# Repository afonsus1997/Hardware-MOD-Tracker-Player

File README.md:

# Hardware MOD Tracker Player

## How to setup the ST ARM toolchain and IDE

* [Download the GNU toolchain from arm](https://developer.arm.com/tools-and-software/open-source-software/developer-tools/gnu-toolchain/gnu-rm/downloads)

* Uninstall old packages 

```sudo apt remove binutils-arm-none-eabi gcc-arm-none-eabi libnewlib-arm-none-eabi```

* Untar package to desired directory (ex: ~/arm/)

```tar -xjvf gcc-arm-none-eabi-xxxxxxxxx```

* Add toolchain to path

```export PATH=$PATH:"PATH TO TOOLCHAIN"/bin/```

* Test arm-gcc

```arm-none-eabi-gcc --version```

### VSCODE Setup

* Install ```stm32-for-vscode``` plugin

* Install ```Cortex-Debug extension``` plugin

### Install STLINK drivers

* Install Libusb

```sudo apt-get install libusb-1.0-0-dev```

* Install stlink ultility

```git clone https://github.com/texane/stlink stlink.git
cd stlink
make
#install binaries:
sudo cp build/Release/st-* /usr/local/bin
#install udev rules
sudo cp etc/udev/rules.d/49-stlinkv* /etc/udev/rules.d/
#and restart udev
sudo udevadm control --reload
```

### Install openOCD

```sudo apt-get install openocd```

### Install STM32CUBEMX (Optional but recommended)

For pinmaps, code generation, etc...

* [Download STM32CUBEMX](https://my.st.com/content/my_st_com/en/products/development-tools/software-development-tools/stm32-software-development-tools/stm32-configurators-and-code-generators/)

* unzip and cd to extracted

* Mark binary as executable

```chmod +x SetupSTM32CubeMX-x.x.x.linux```

* Run binary

```./SetupSTM32CubeMX-x.x.x.linux```

* Go through installation process on GUI

## How to flash STM project

### Using VScode

* Open project folder

* Open command list (Ctrl+Shift+p)

* Type ```stm32``` and choose an option

### Using make

* Build

```make -f STM32Make.make```

* Build and flash

```make -f STM32Make.make flash```

* Clean 

```make -f STM32Make.make clean```

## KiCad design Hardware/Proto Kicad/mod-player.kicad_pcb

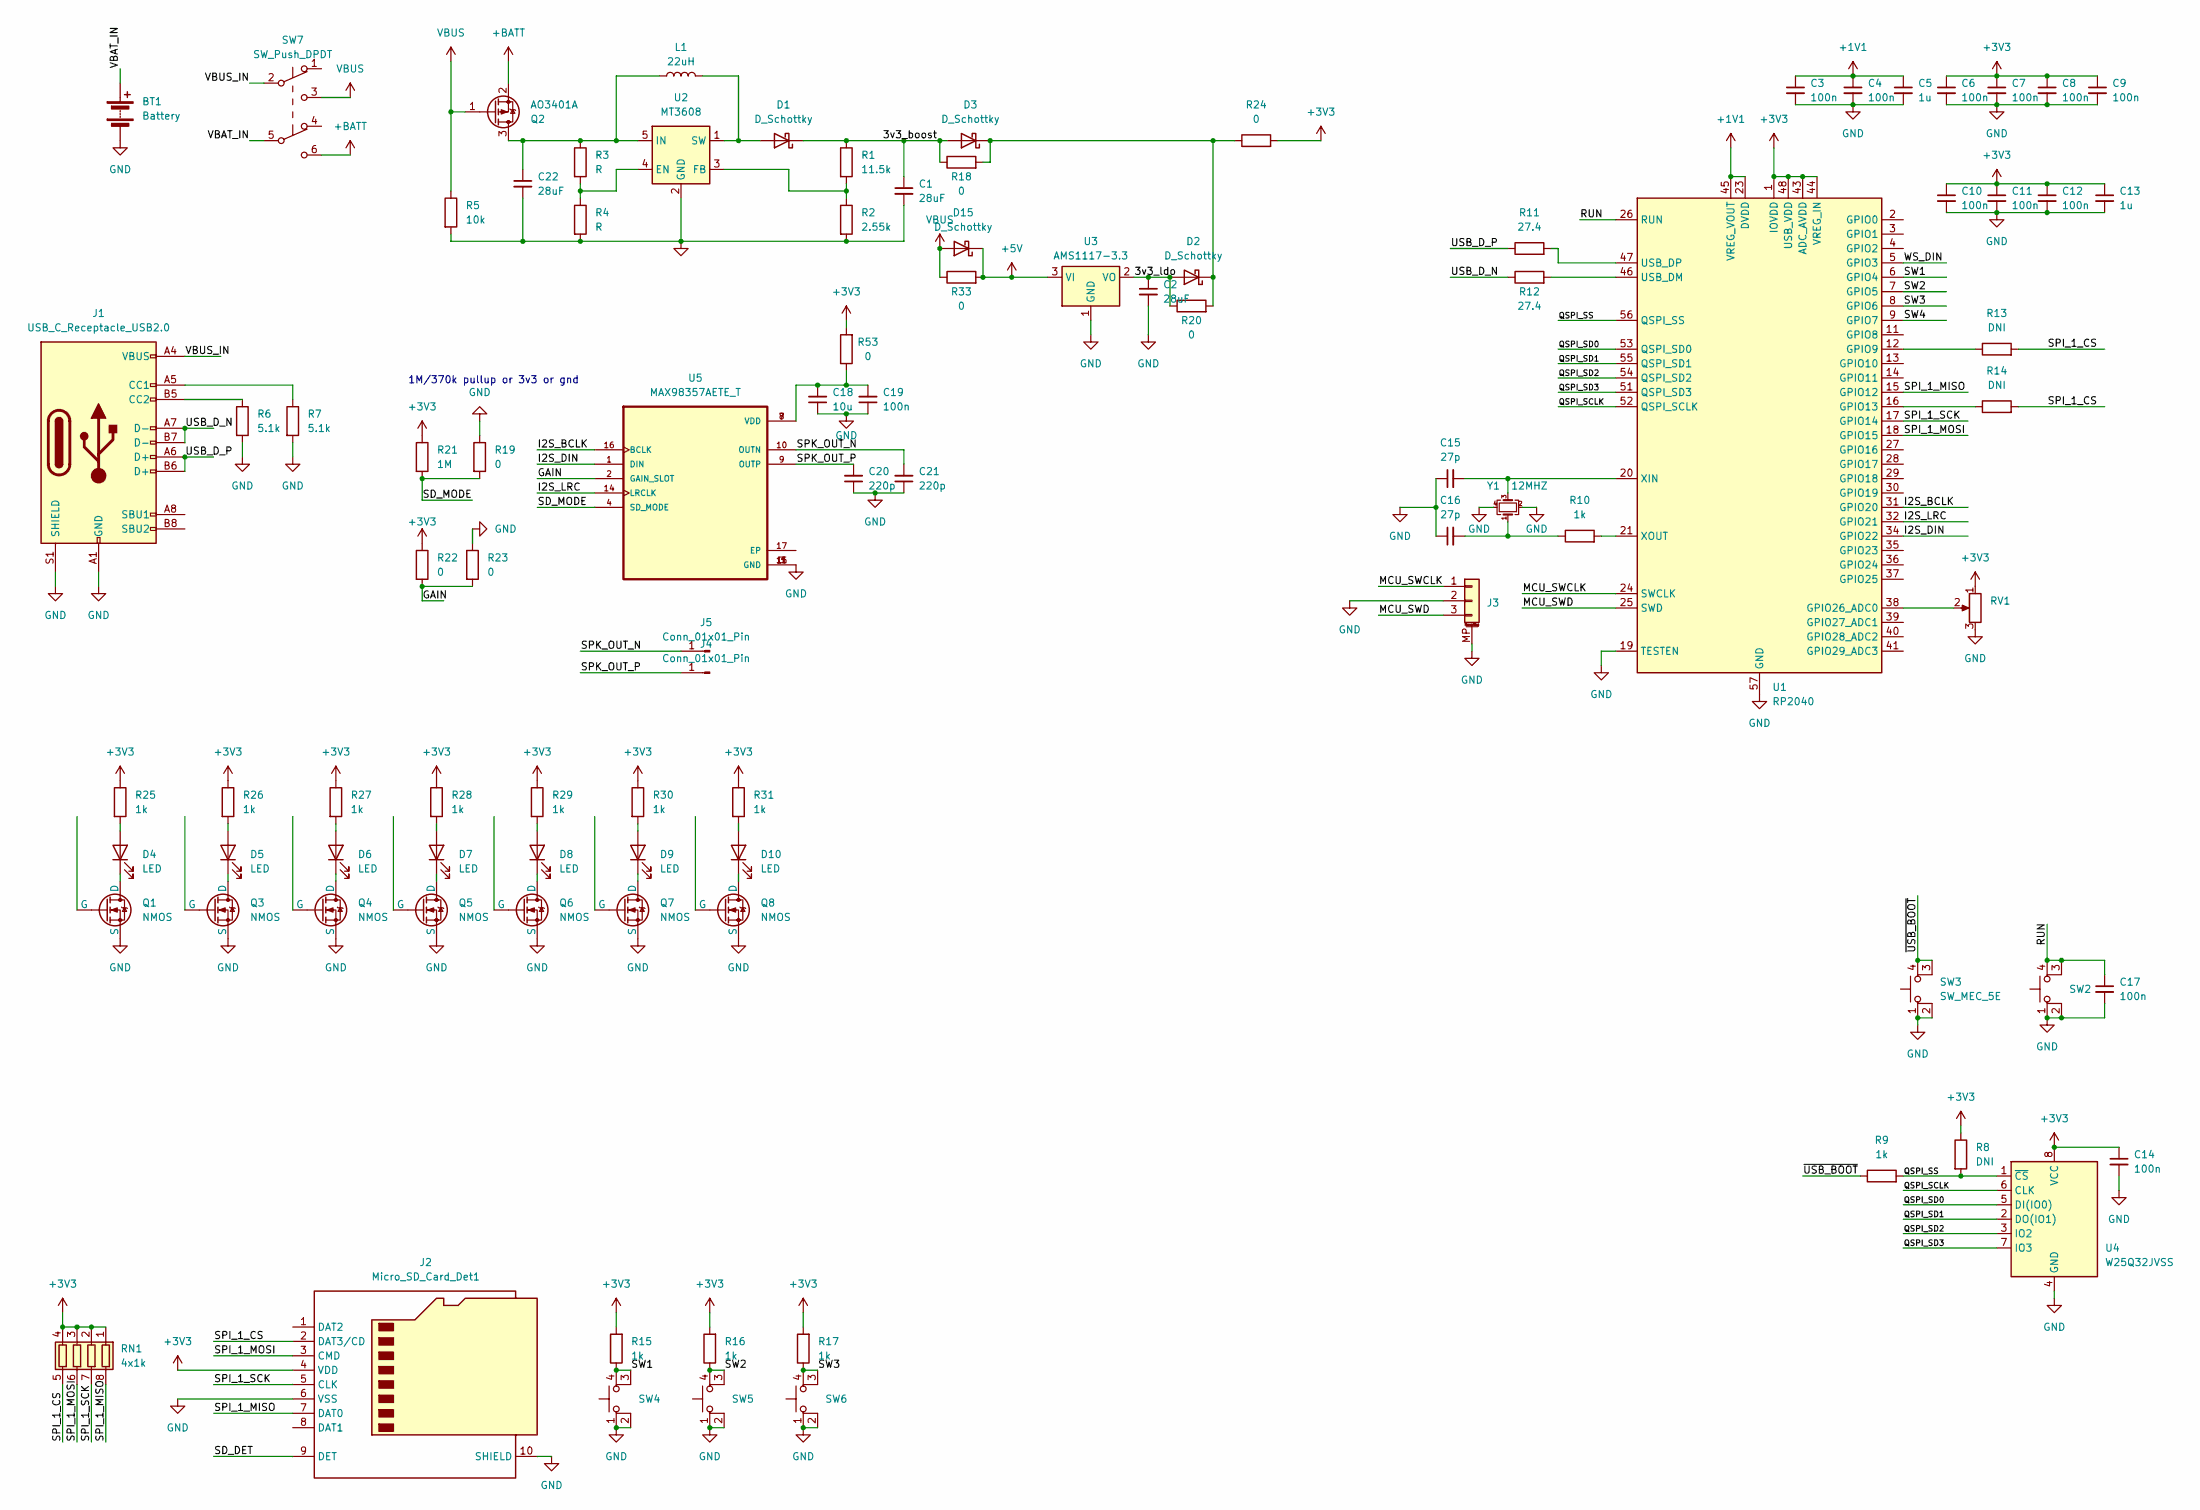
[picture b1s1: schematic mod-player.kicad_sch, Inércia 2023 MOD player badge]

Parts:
BT1: Battery; AAA-HOLDER-THD
C1, C2, C22: 28uF; C_0603_1608Metric
C3, C4, C6, C7, C8, C9, C10, C11, C12, C14, C17, C19: 100n; C_0603_1608Metric
C5, C13: 1u; C_0603_1608Metric
C15, C16: 27p; C_0603_1608Metric
C18: 10u; C_0603_1608Metric
C20, C21: 220p; C_0603_1608Metric
D1, D2, D3, D15: D_Schottky; D_SOD-123
D4, D5, D6, D7, D8, D9, D10: LED; 1206_reverse_xinglight
J1: USB_C_Receptacle_USB2.0; USB_C_Receptacle_HCTL_HC-TYPE-C-16P-01A
J2: Micro_SD_Card_Det1; J_sd_micro_socket
J3: Conn_01x03_MountingPin; JST_SH_SM03B-SRSS-TB_1x03-1MP_P1.00mm_Horizontal
J4, J5: Conn_01x01_Pin; TestPoint_Keystone_5019_Minature
L1: 22uH; L_Changjiang_FNR5040S
Q1, Q3, Q4, Q5, Q6, Q7, Q8: NMOS; SOT-23
Q2: AO3401A; SOT-23
R1: 11.5k; R_0603_1608Metric
R2: 2.55k; R_0603_1608Metric
R3, R4: R; R_0603_1608Metric
R5: 10k; R_0603_1608Metric
R6, R7: 5.1k; R_0603_1608Metric
R8, R13, R14: DNI; R_0603_1608Metric
R9, R15, R16, R17, R25, R26, R27, R28, R29, R30, R31: 1k; R_0603_1608Metric
R10: 1k; R_0402_1005Metric
R11, R12: 27.4; R_0402_1005Metric
R18, R19, R20, R22, R23, R24, R33, R53: 0; R_0603_1608Metric
R21: 1M; R_0603_1608Metric
RN1: 4x1k; R_Array_Convex_4x0402
RV1: R_Potentiometer; gear-dial-pot-3pin
SW2, SW3, SW4, SW5, SW6: SW_MEC_5E; SW_SKRPACE010
SW7: SW_Push_DPDT; SS-3235S-L2
U1: RP2040; QFN-56-1EP_7x7mm_P0.4mm_EP3.2x3.2mm
U2: MT3608; SOT-23-6
U3: AMS1117-3.3; SOT-223-3_TabPin2
U4: W25Q32JVSS; SOIC-8_5.23x5.23mm_P1.27mm
U5: MAX98357AETE_T; QFN50P300X300X80-17N
Y1: 12MHZ; Crystal_SMD_3225-4Pin_3.2x2.5mm

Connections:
+1V1: C3.1, C4.1, C5.1, U1.23 (DVDD), U1.45 (VREG_VOUT), U1.50 (DVDD)
+3V3: C6.1, C7.1, C8.1, C9.1, C10.1, C11.1, C12.1, C13.1, C14.1, J2.4 (VDD), R8.1, R15.2, R16.2, R17.2, R21.1, R22.1, R24.2, R25.1, R26.1, R27.1, R28.1, R29.1, R30.1, R31.1, R53.2, RN1.1 (R1.1), RN1.2 (R2.1), RN1.3 (R3.1), RN1.4 (R4.1), RV1.1, U1.1 (IOVDD), U1.10 (IOVDD), U1.22 (IOVDD), U1.33 (IOVDD), U1.42 (IOVDD), U1.43 (ADC_AVDD), U1.44 (VREG_IN), U1.48 (USB_VDD), U1.49 (IOVDD), U4.8 (VCC)
+5V: D15.1 (K), R33.2, U3.3 (VI)
+BATT: Q2.2 (S), SW7.6 (C)
/3v3_boost: C1.1, D1.1 (K), D3.2 (A), R1.1, R18.1
/3v3_ldo: C2.1, D2.2 (A), R20.1, U3.2 (VO)
/GAIN: R22.2, R23.2, U5.2 (GAIN_SLOT)
/I2S_BCLK: U1.31 (GPIO20), U5.16 (BCLK)
/I2S_DIN: U1.34 (GPIO22), U5.1 (DIN)
/I2S_LRC: U1.32 (GPIO21), U5.14 (LRCLK)
/MCU_SWCLK: J3.1, U1.24 (SWCLK)
/MCU_SWD: J3.3, U1.25 (SWD)
/QSPI_SCLK: U1.52 (QSPI_SCLK), U4.6 (CLK)
/QSPI_SD0: U1.53 (QSPI_SD0), U4.5 (DI(IO0))
/QSPI_SD1: U1.55 (QSPI_SD1), U4.2 (DO(IO1))
/QSPI_SD2: U1.54 (QSPI_SD2), U4.3 (IO2)
/QSPI_SD3: U1.51 (QSPI_SD3), U4.7 (IO3)
/QSPI_SS: R8.2, R9.2, U1.56 (QSPI_SS), U4.1 (~CS)
/RUN: C17.1, SW2.3 (K), SW2.4 (A), U1.26 (RUN)
/SD_DET: J2.9 (DET)
/SD_MODE: R19.2, R21.2, U5.4 (SD_MODE)
/SPI_1_CS: J2.2 (DAT3/CD), R13.2, R14.2, RN1.5 (R4.2)
/SPI_1_MISO: J2.7 (DAT0), RN1.8 (R1.2), U1.15 (GPIO12)
/SPI_1_MOSI: J2.3 (CMD), RN1.6 (R3.2), U1.18 (GPIO15)
/SPI_1_SCK: J2.5 (CLK), RN1.7 (R2.2), U1.17 (GPIO14)
/SPK_OUT_N: C21.2, J5.1, U5.10 (OUTN)
/SPK_OUT_P: C20.2, J4.1, U5.9 (OUTP)
/SW1: R15.1, SW4.3 (K), SW4.4 (A), U1.6 (GPIO4)
/SW2: R16.1, SW5.3 (K), SW5.4 (A), U1.7 (GPIO5)
/SW3: R17.1, SW6.3 (K), SW6.4 (A), U1.8 (GPIO6)
/SW4: U1.9 (GPIO7)
/USB_D_N: J1.A7 (D-), J1.B7 (D-), R12.1
/USB_D_P: J1.A6 (D+), J1.B6 (D+), R11.1
/VBAT_IN: BT1.1 (+), SW7.5 (B)
/VBUS_IN: J1.A4 (VBUS), J1.A9 (VBUS), J1.B4 (VBUS), J1.B9 (VBUS), SW7.2 (B)
/WS_DIN: U1.5 (GPIO3)
/~USB_BOOT: R9.1, SW3.3 (K), SW3.4 (A)
GND: BT1.2 (-), C1.2, C2.2, C3.2, C4.2, C5.2, C6.2, C7.2, C8.2, C9.2, C10.2, C11.2, C12.2, C13.2, C14.2, C15.1, C16.1, C17.2, C18.1, C19.1, C20.1, C21.1, C22.2, J1.A1 (GND), J1.A12 (GND), J1.B1 (GND), J1.B12 (GND), J1.S1 (SHIELD), J2.6 (VSS), J2.10 (SHIELD), J3.2, J3.MP (MountPin), Q1.3 (S), Q3.3 (S), Q4.3 (S), Q5.3 (S), Q6.3 (S), Q7.3 (S), Q8.3 (S), R2.2, R4.2, R5.2, R6.2, R7.2, R19.1, R23.1, RV1.3, SW2.1, SW2.2, SW3.1, SW3.2, SW4.1, SW4.2, SW5.1, SW5.2, SW6.1, SW6.2, U1.19 (TESTEN), U1.57 (GND), U2.2 (GND), U3.1 (GND), U4.4 (GND), U5.3 (GND), U5.11 (GND), U5.15 (GND), Y1.2, Y1.4
unnamed: C16.2, R10.1, Y1.1
unnamed: C18.2, C19.2, R53.1, U5.7 (VDD), U5.8 (VDD)
unnamed: D1.2 (A), L1.2, U2.1 (SW)
unnamed: D2.1 (K), D3.1 (K), R18.2, R20.2, R24.1
unnamed: D4.2 (A), R25.2
unnamed: D4.1 (K), Q1.1 (D)
unnamed: D5.2 (A), R26.2
unnamed: D5.1 (K), Q3.1 (D)
unnamed: D6.2 (A), R27.2
unnamed: D6.1 (K), Q4.1 (D)
unnamed: D7.2 (A), R28.2
unnamed: D7.1 (K), Q5.1 (D)
unnamed: D8.2 (A), R29.2
unnamed: D8.1 (K), Q6.1 (D)
unnamed: D9.2 (A), R30.2
unnamed: D9.1 (K), Q7.1 (D)
unnamed: D10.2 (A), R31.2
unnamed: D10.1 (K), Q8.1 (D)
unnamed: J1.A5 (CC1), R7.1
unnamed: J1.B5 (CC2), R6.1
unnamed: C22.1, L1.1, Q2.3 (D), R3.1, U2.5 (IN)
unnamed: R13.1, U1.12 (GPIO9)
unnamed: R14.1, U1.16 (GPIO13)
unnamed: RV1.2, U1.38 (GPIO26_ADC0)
unnamed: R12.2, U1.46 (USB_DM)
unnamed: R11.2, U1.47 (USB_DP)
unnamed: C15.2, U1.20 (XIN), Y1.3
unnamed: R10.2, U1.21 (XOUT)
unnamed: R3.2, R4.1, U2.4 (EN)
unnamed: R1.2, R2.1, U2.3 (FB)
VBUS: D15.2 (A), Q2.1 (G), R5.1, R33.1, SW7.3 (C)

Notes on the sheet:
1M/370k pullup or 3v3 or gnd

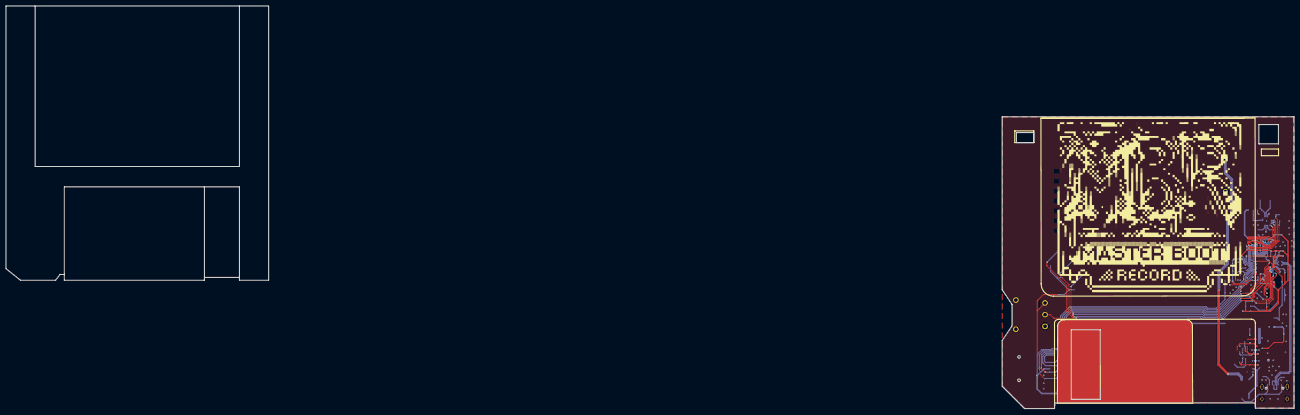
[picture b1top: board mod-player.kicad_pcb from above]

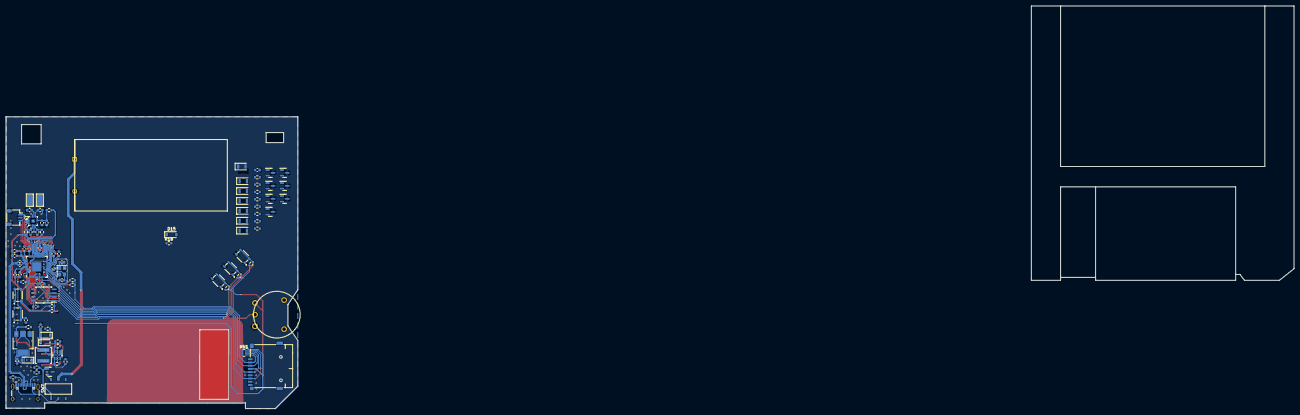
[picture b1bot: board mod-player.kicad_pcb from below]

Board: 4 copper layers, 100.0 x 100.0 mm, 95 parts (95 on the bottom side), 66 nets.

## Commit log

2019-12-26 added development project for 32f4disco board
2019-12-26 enabled SPI1
2019-12-26 Added Lib to makefile
2019-12-26 Added build to gitignore
2020-01-04 Added instructions to README
2020-01-04 minor changes to readme
2020-01-04 Added BSP board drivers for DISCO board. Setup LCD and audio
2023-10-26 added proto hardware
2023-10-31 hardware update
2023-11-02 more hardware
2023-11-02 added new hw projects
2023-11-03 boards exported and sent to fab
